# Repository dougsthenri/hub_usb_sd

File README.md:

# hub_usb_sd
PCB project for an SD card reader with 2-port USB hub and I²C bridge.

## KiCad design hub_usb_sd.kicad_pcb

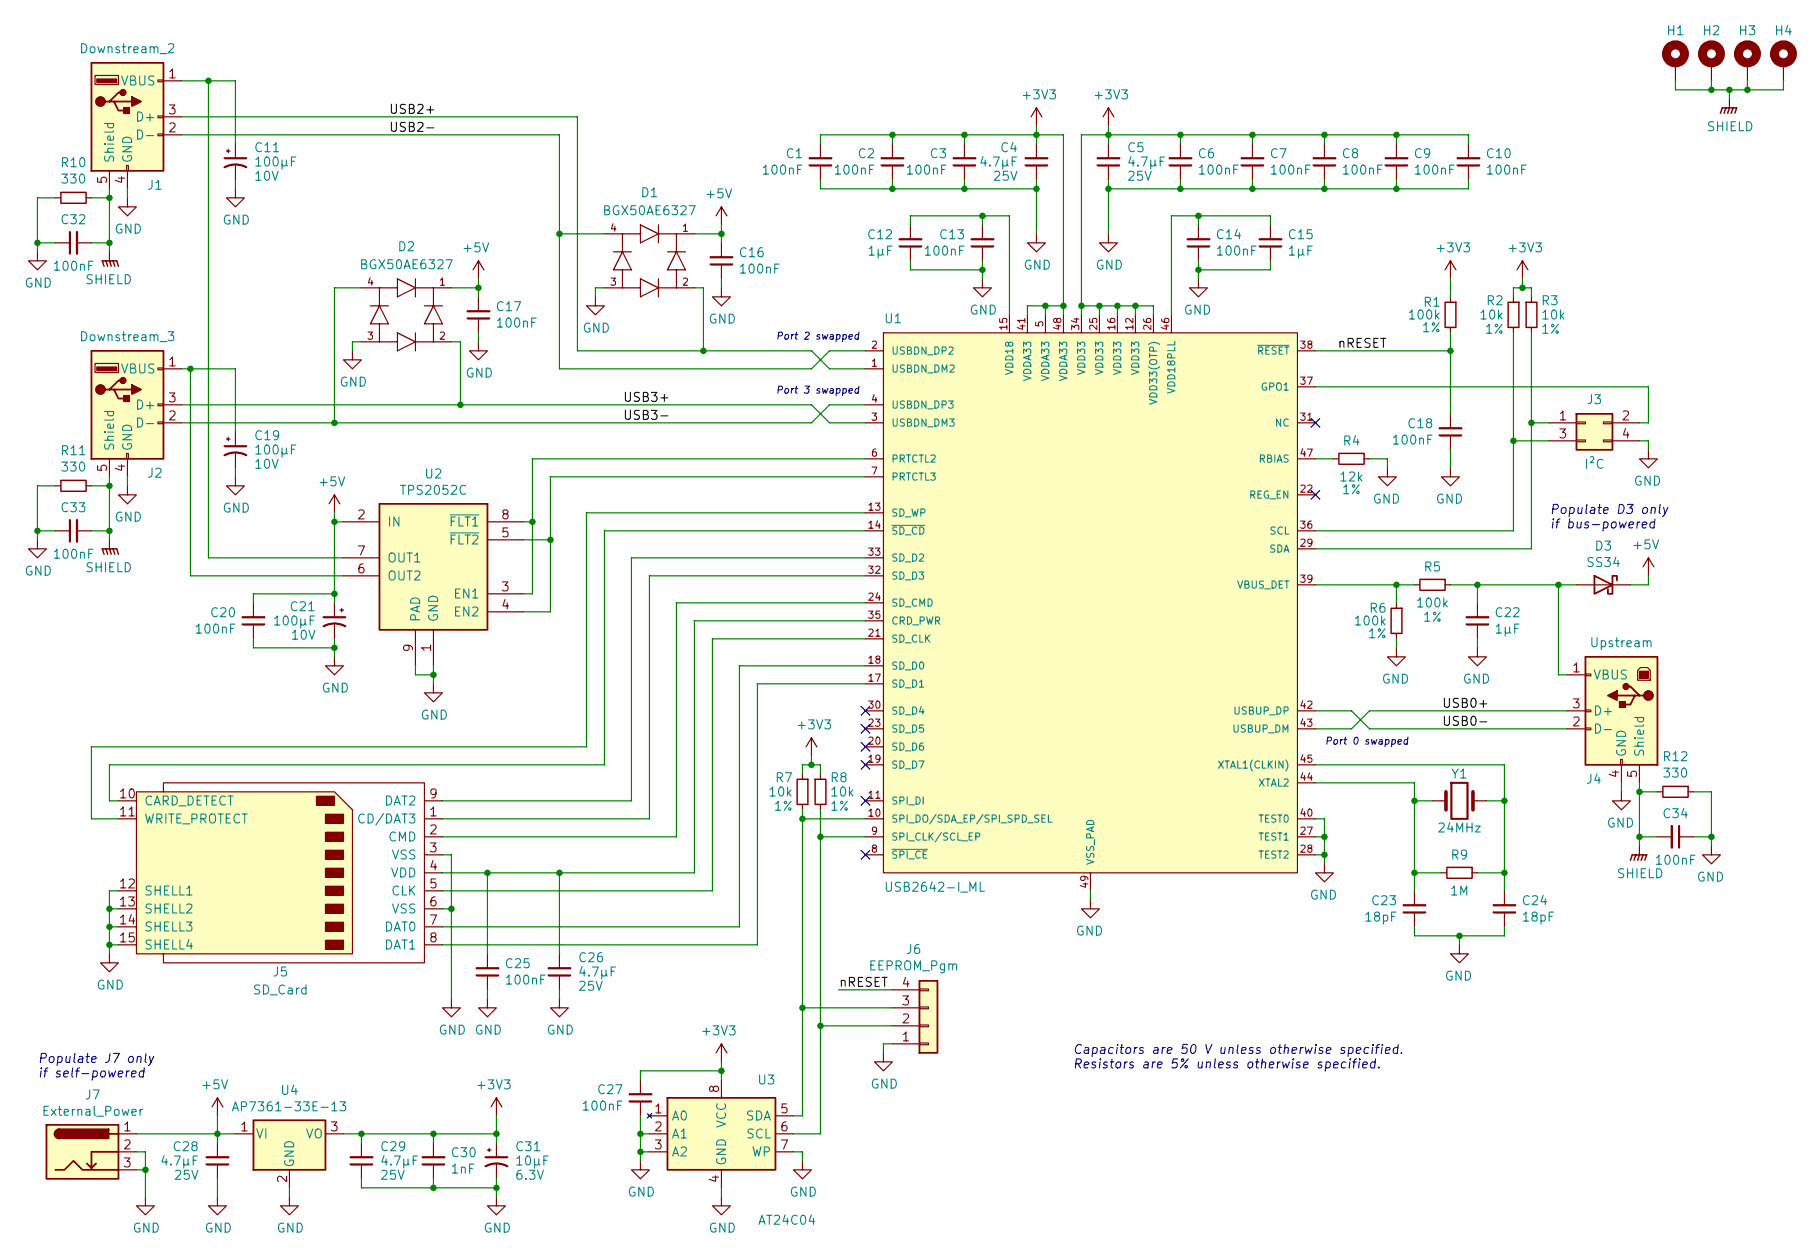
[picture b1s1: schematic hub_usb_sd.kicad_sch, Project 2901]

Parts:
C1, C2, C3, C6, C7, C8, C9, C10, C13, C14, C16, C17, C18, C20, C25, C27: 100nF; C_0805_2012Metric; Part# C0805C104K5RACTU
C4, C5, C26, C28, C29: 4.7µF; C_0805_2012Metric; Part# 08054,7UF25V
C11, C19, C21: 100µF; CP_EIA-3528-21_Kemet-B; Voltage 10V; Part# TMCMB1A107MTRF
C12, C15, C22: 1µF; C_0805_2012Metric; Part# 08051UF50V
C23, C24: 18pF; C_0603_1608Metric; Part# 060318PF50V
C30: 1nF; C_0603_1608Metric; Part# 06031NF50V
C31: 10µF; CP_EIA-3216-18_Kemet-A; Voltage 6.3V; Part# T491A106K006AT
C32, C33, C34: 100nF; C_0603_1608Metric; Part# 0603100NF50V
D1, D2: BGX50AE6327; Part# BGX 50A E6327
D3: SS34; D_SMC; Part# SS34
H1, H2, H3, H4: MountingHole_Pad; MountingHole_2.2mm_M2_Pad_Via
J1: Downstream_2; AF90_protruded_6_mm; Part# AF90
J2: Downstream_3; AF90_protruded_6_mm; Part# AF90
J3: I²C; PinHeader_2x02_P2.54mm_Horizontal_protruded_6_mm
J4: Upstream; USB_B_OST_USB-B1HSxx_Horizontal_Protruded_6_mm; Part# YH-USB03
J5: SD_Card; GCT_MEM1055-00-280-01-B; Part# 1138022
J6: EEPROM_Pgm; PinHeader_1x04_P2.54mm_Vertical
J7: External_Power; BarrelJack_DC-005_protruded_6_mm; Part# DC-005
R1, R5, R6: 100k; R_0805_2012Metric; Tolerance 1%; Part# CRCW0805100KFKEA
R2, R3, R7, R8: 10k; R_0805_2012Metric; Part# 08051%10K
R4: 12k; R_0805_2012Metric; Part# MC0805WAF1202T5E-TC
R9: 1M; R_0603_1608Metric; Part# 0603-1MOHM
R10, R11, R12: 330; R_0603_1608Metric; Part# 0603-330OHMS
U1: USB2642-I_ML; Microchip_USB2642-I_ML; Part# USB2642-I/ML-SEU
U2: TPS2052C; TI_DGN0008G; Part# TPS2052CDGNR
U3: AT24C04; Atmel_AT24C04BN; Part# AT24C04N-10SU-2.7
U4: AP7361-33E-13; SOT-223-3_TabPin2; Part# AP7361-33E-13
Y1: XRCGB24M000F0L00R0; Murata_XRCGB24M000F0L00R0; Part# XRCGB24M000F0L00R0

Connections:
+3V3: C1.2, C2.2, C3.2, C4.2, C5.2, C6.2, C7.2, C8.2, C9.2, C10.2, C27.2, C29.2, C30.2, C31.1, R1.1, R2.1, R3.1, R7.1, R8.1, U1.5 (VDDA33), U1.12 (VDD33), U1.16 (VDD33), U1.25 (VDD33), U1.26 (VDD33(OTP)), U1.34 (VDD33), U1.41 (VDDA33), U1.48 (VDDA33), U3.8 (VCC), U4.3 (VO)
+5V: C16.2, C17.2, C20.2, C21.1, C28.2, D1.1, D2.1, D3.1 (K), J7.1, U2.2 (IN), U4.1 (VI)
/USB0+: J4.3 (D+), U1.43 (USBUP_DM)
/USB0-: J4.2 (D-), U1.42 (USBUP_DP)
/USB2+: D1.2, J1.3 (D+), U1.1 (USBDN_DM2)
/USB2-: D1.4, J1.2 (D-), U1.2 (USBDN_DP2)
/USB3+: D2.2, J2.3 (D+), U1.3 (USBDN_DM3)
/USB3-: D2.4, J2.2 (D-), U1.4 (USBDN_DP3)
/nRESET: C18.2, J6.4, R1.2, U1.38 (~RESET)
GND: C1.1, C2.1, C3.1, C4.1, C5.1, C6.1, C7.1, C8.1, C9.1, C10.1, C11.2, C12.1, C13.1, C14.1, C15.1, C16.1, C17.1, C18.1, C19.2, C20.1, C21.2, C22.1, C23.1, C24.1, C25.1, C26.1, C27.1, C28.1, C29.1, C30.1, C31.2, C32.1, C33.1, C34.1, D1.3, D2.3, J1.4 (GND), J2.4 (GND), J3.4, J4.4 (GND), J5.3 (VSS), J5.6 (VSS), J5.12 (SHELL1), J5.13 (SHELL2), J5.14 (SHELL3), J5.15 (SHELL4), J6.1, J7.2, J7.3, R4.1, R6.2, R10.1, R11.1, R12.1, U1.27 (TEST1), U1.28 (TEST2), U1.40 (TEST0), U1.49 (VSS_PAD), U2.1 (GND), U2.9 (PAD), U3.2 (A1), U3.3 (A2), U3.4 (GND), U3.7 (WP), U4.2 (GND)
unnamed: C22.2, D3.2 (A), J4.1 (VBUS), R5.1
unnamed: C11.1, J1.1 (VBUS), U2.7 (OUT1)
unnamed: C19.1, J2.1 (VBUS), U2.6 (OUT2)
unnamed: J3.1, R3.2, U1.29 (SDA)
unnamed: J3.2, U1.37 (GPO1)
unnamed: J3.3, R2.2, U1.36 (SCL)
unnamed: J5.10 (CARD_DETECT), U1.14 (~SD_CD)
unnamed: J5.1 (CD/DAT3), U1.32 (SD_D3)
unnamed: J5.5 (CLK), U1.21 (SD_CLK)
unnamed: J5.2 (CMD), U1.24 (SD_CMD)
unnamed: J5.7 (DAT0), U1.18 (SD_D0)
unnamed: J5.8 (DAT1), U1.17 (SD_D1)
unnamed: J5.9 (DAT2), U1.33 (SD_D2)
unnamed: C25.2, C26.2, J5.4 (VDD), U1.35 (CRD_PWR)
unnamed: J5.11 (WRITE_PROTECT), U1.13 (SD_WP)
unnamed: J6.2, R8.2, U1.9 (SPI_CLK/SCL_EP), U3.6 (SCL)
unnamed: J6.3, R7.2, U1.10 (SPI_DO/SDA_EP/SPI_SPD_SEL), U3.5 (SDA)
unnamed: U1.6 (PRTCTL2), U2.3 (EN1), U2.8 (~FLT1)
unnamed: U1.7 (PRTCTL3), U2.4 (EN2), U2.5 (~FLT2)
unnamed: R4.2, U1.47 (RBIAS)
unnamed: R5.2, R6.1, U1.39 (VBUS_DET)
unnamed: C12.2, C13.2, U1.15 (VDD18)
unnamed: C14.2, C15.2, U1.46 (VDD18PLL)
unnamed: C24.2, R9.1, U1.45 (XTAL1(CLKIN)), Y1.3 (Crystal_terminal)
unnamed: C23.2, R9.2, U1.44 (XTAL2), Y1.1 (Crystal_terminal)
SHIELD: C32.2, C33.2, C34.2, H1.1, H2.1, H3.1, H4.1, J1.5 (Shield), J2.5 (Shield), J4.5 (Shield), R10.2, R11.2, R12.2

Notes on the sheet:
Port 0 swapped
Capacitors are 50 V unless otherwise specified. Resistors are 5% unless otherwise specified.
Port 3 swapped
Port 2 swapped
Populate D3 only if bus-powered
Populate J7 only if self-powered

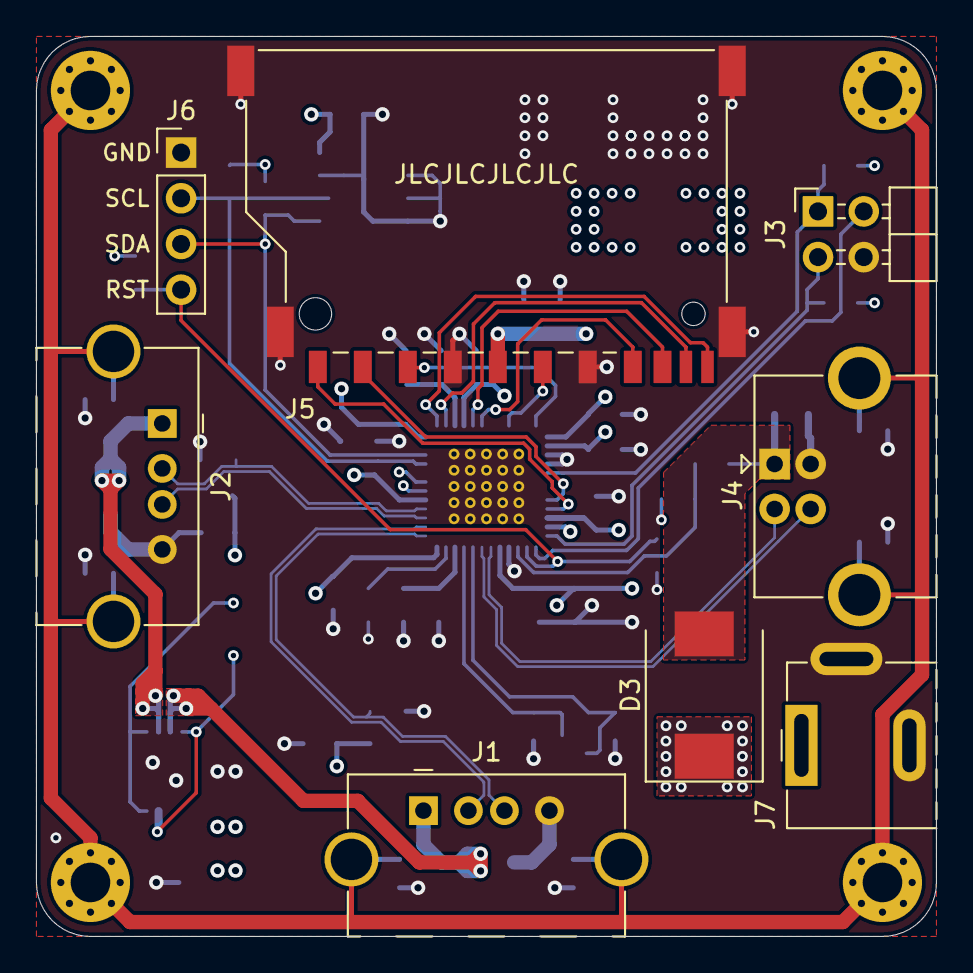
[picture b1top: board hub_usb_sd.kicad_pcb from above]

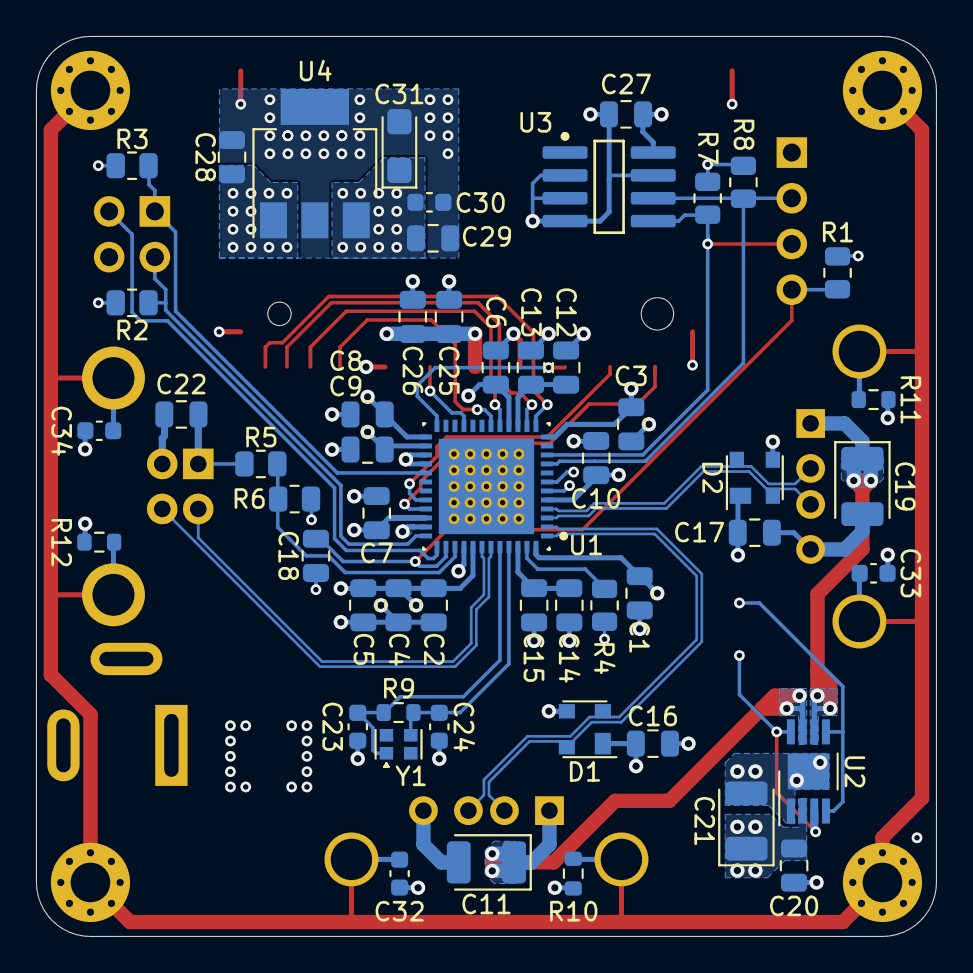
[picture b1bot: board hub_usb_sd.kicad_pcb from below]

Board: 4 copper layers, 50.0 x 50.0 mm, 65 parts (53 on the bottom side), 36 nets.

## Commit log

2020-12-19 Added production remarks to schematic
2020-12-20 Improved ground plane under U2 and corrected the positioning of C32-34
2020-12-21 Updated board layout to accommodate new power supply connector
2020-12-21 Optimized trace under C18
2024-03-12 Upgraded project to Kicad 8.0. Defined part# fields. Further corrections pending
2024-03-27 Backup directory and local project settings file removed from versioning
2025-03-24 Created README.md
2025-03-24 Added PCB rendering image
2025-03-24 Fixed a typo on README file
2025-04-03 Reestructured repository for publishing on GitHub
